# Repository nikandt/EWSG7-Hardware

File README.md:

# PP7 Hardware

This is the hardware repository of sensor probe test module, developed by student team with Aalto University.
<br>The designed system automates several tedious tasks within sensor application development by allowing easy flashing of devices without making physical changes to the test environment.

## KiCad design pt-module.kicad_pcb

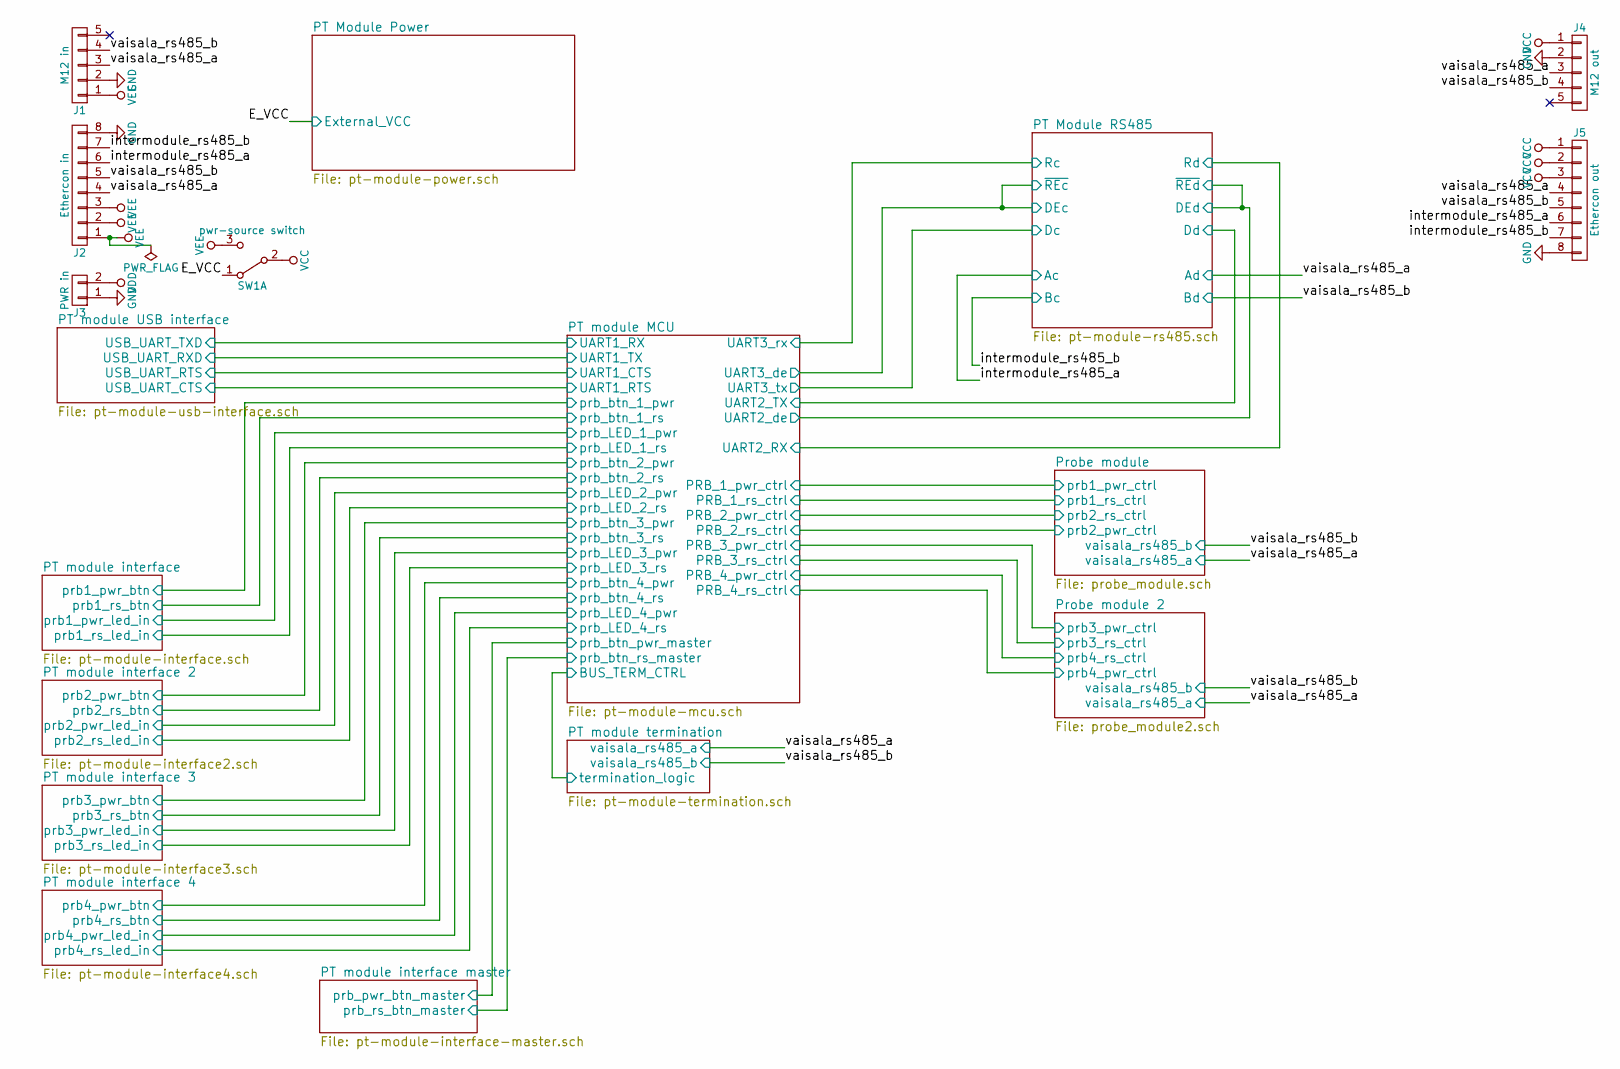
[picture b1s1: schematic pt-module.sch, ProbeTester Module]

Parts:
J1: M12 in; Hirose_DF13C-05P-1.25V_05x1.25mm_Straight
J2: Ethercon in; Hirose_DF13C-08P-1.25V_08x1.25mm_Straight
J3: PWR in; Hirose_DF13C-02P-1.25V_02x1.25mm_Straight
J4: M12 out; Hirose_DF13C-05P-1.25V_05x1.25mm_Straight
J5: Ethercon out; Hirose_DF13C-08P-1.25V_08x1.25mm_Straight
SW1: pwr-source switch; Hirose_DF13C-03P-1.25V_03x1.25mm_Straight

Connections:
/E_VCC: SW1.1 (A); also elsewhere on the board
/intermodule_rs485_a: J2.6, J5.6; also elsewhere on the board
/intermodule_rs485_b: J2.7, J5.7; also elsewhere on the board
/vaisala_rs485_a: J1.3, J2.4, J4.3, J5.4; also elsewhere on the board
/vaisala_rs485_b: J1.4, J2.5, J4.4, J5.5; also elsewhere on the board
GND: J1.2, J2.8, J3.1, J4.2, J5.8; also elsewhere on the board
VCC: J4.1, J5.1, J5.2, J5.3, SW1.2 (B); also elsewhere on the board
VDD: J3.2; also elsewhere on the board
VEE: J1.1, J2.1, J2.2, J2.3, SW1.3 (C)

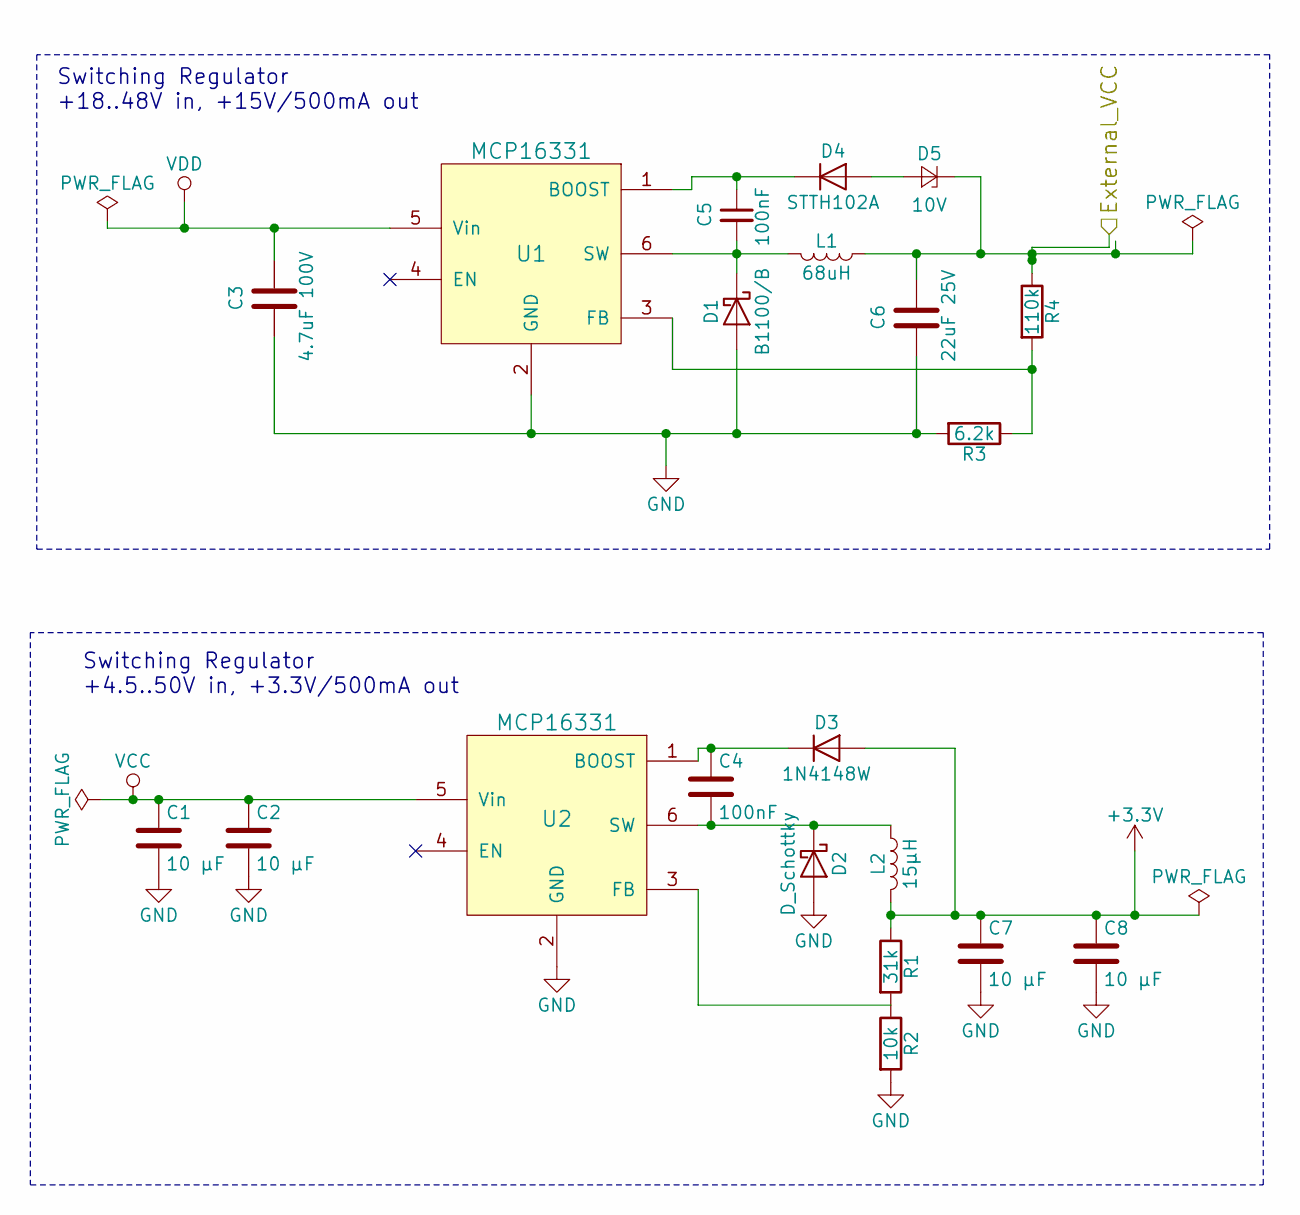
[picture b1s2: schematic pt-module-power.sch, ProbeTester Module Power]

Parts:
C1, C2, C7, C8: 10 µF; C_1206_HandSoldering
C3: 4.7uF 100V; C_1206_HandSoldering
C4, C5: 100nF; C_1206_HandSoldering
C6: 22uF 25V; C_1206_HandSoldering
D1: B1100/B; D_SMB
D2: D_Schottky; D_SMA
D3: 1N4148W; D_SOD-123F
D4: STTH102A; D_SMA
D5: 10V; D_SOD-323
L1: 68uH; L_7.3x7.3_H4.5
L2: 15µH; SM-4.3x4.3
R1: 31k; R_1206_HandSoldering
R2: 10k; R_1206_HandSoldering
R3: 6.2k; R_1206_HandSoldering
R4: 110k; R_1206_HandSoldering
U1, U2: MCP16331; SOT-23-6

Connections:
/E_VCC: C6.1, D5.1 (K), L1.1, R4.1; also elsewhere on the board
GND: C1.2, C2.2, C3.2, C6.2, C7.2, C8.2, D1.2 (A), D2.2 (A), R2.2, R3.2, U1.2 (GND), U2.2 (GND); also elsewhere on the board
unnamed: C4.1, D3.1 (K), U2.1 (BOOST)
unnamed: C4.2, D2.1 (K), L2.1, U2.6 (SW)
unnamed: C5.1, D4.1 (K), U1.1 (BOOST)
unnamed: C5.2, D1.1 (K), L1.2, U1.6 (SW)
unnamed: D4.2 (A), D5.2 (A)
unnamed: R1.2, R2.1, U2.3 (FB)
unnamed: R3.1, R4.2, U1.3 (FB)
VCC: C1.1, C2.1, U2.5 (Vin); also elsewhere on the board
VDD: C3.1, U1.5 (Vin); also elsewhere on the board

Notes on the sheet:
Switching Regulator +4.5..50V in, +3.3V/500mA out
Switching Regulator +18..48V in, +15V/500mA out

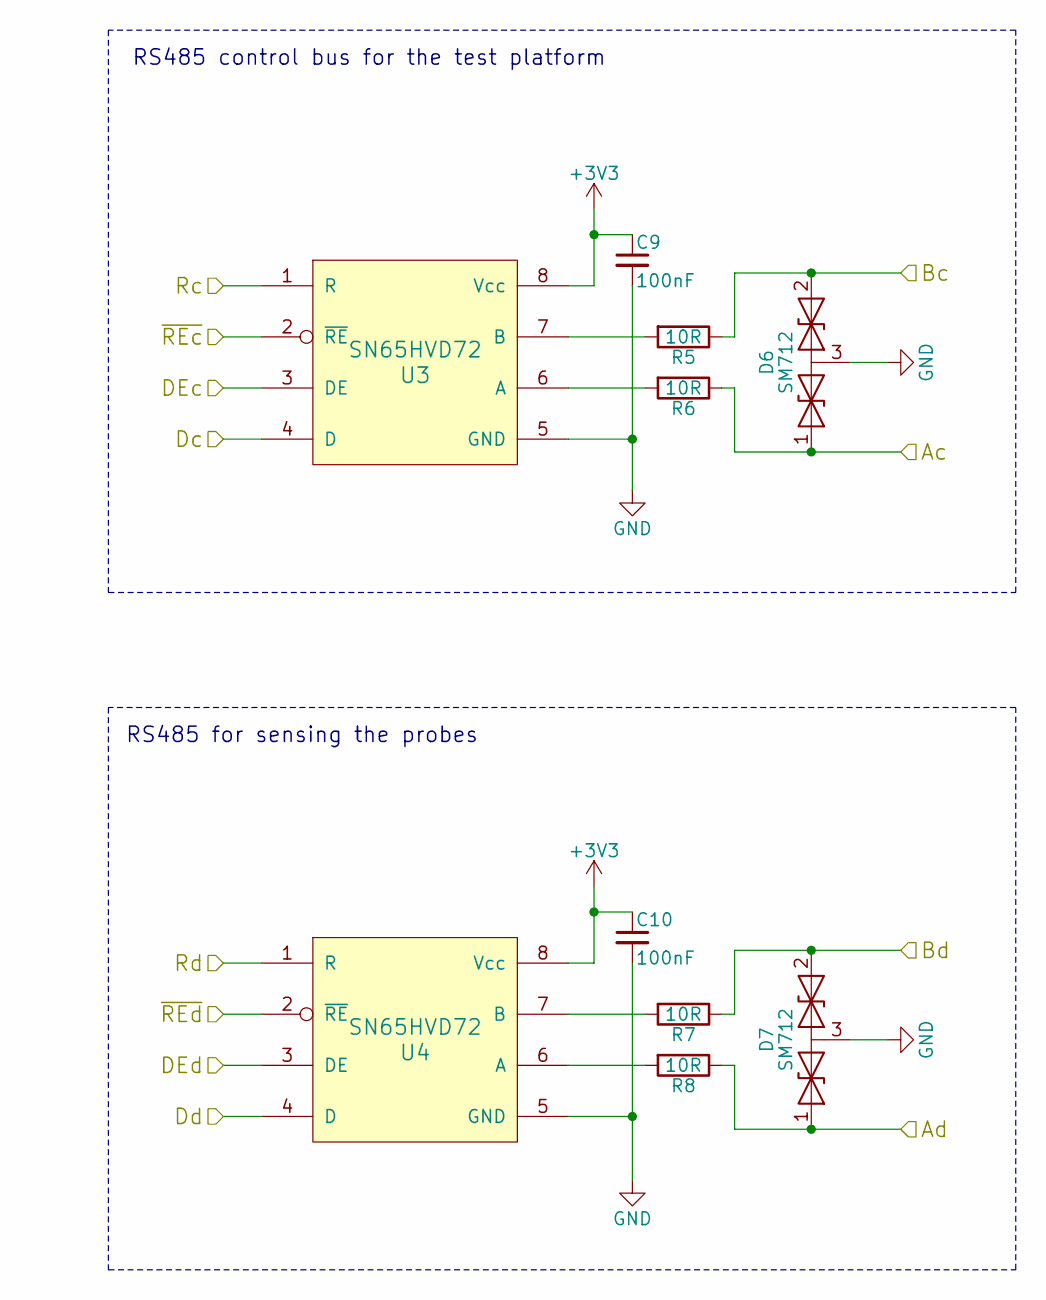
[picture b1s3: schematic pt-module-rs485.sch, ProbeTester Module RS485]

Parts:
C9, C10: 100nF; C_1206_HandSoldering
D6, D7: SM712; SOT-23_Handsoldering
R5, R6, R7, R8: 10R; R_0805_HandSoldering
U3, U4: SN65HVD72; SOIC-8_3.9x4.9mm_Pitch1.27mm

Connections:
/PT Module RS485/DEc: U3.2 (~RE), U3.3 (DE); also elsewhere on the board
/PT Module RS485/DEd: U4.2 (~RE), U4.3 (DE); also elsewhere on the board
/PT Module RS485/Dc: U3.4 (D); also elsewhere on the board
/PT Module RS485/Dd: U4.4 (D); also elsewhere on the board
/PT Module RS485/Rc: U3.1 (R); also elsewhere on the board
/PT Module RS485/Rd: U4.1 (R); also elsewhere on the board
/intermodule_rs485_a: D6.1 (A1), R6.1; also elsewhere on the board
/intermodule_rs485_b: D6.2 (A2), R5.1; also elsewhere on the board
/vaisala_rs485_a: D7.1 (A1), R8.1; also elsewhere on the board
/vaisala_rs485_b: D7.2 (A2), R7.1; also elsewhere on the board
GND: C9.2, C10.2, D6.3 (common), D7.3 (common), U3.5 (GND), U4.5 (GND); also elsewhere on the board
unnamed: R5.2, U3.7 (B)
unnamed: R6.2, U3.6 (A)
unnamed: R7.2, U4.7 (B)
unnamed: R8.2, U4.6 (A)

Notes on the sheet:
RS485 for sensing the probes
RS485 control bus for the test platform

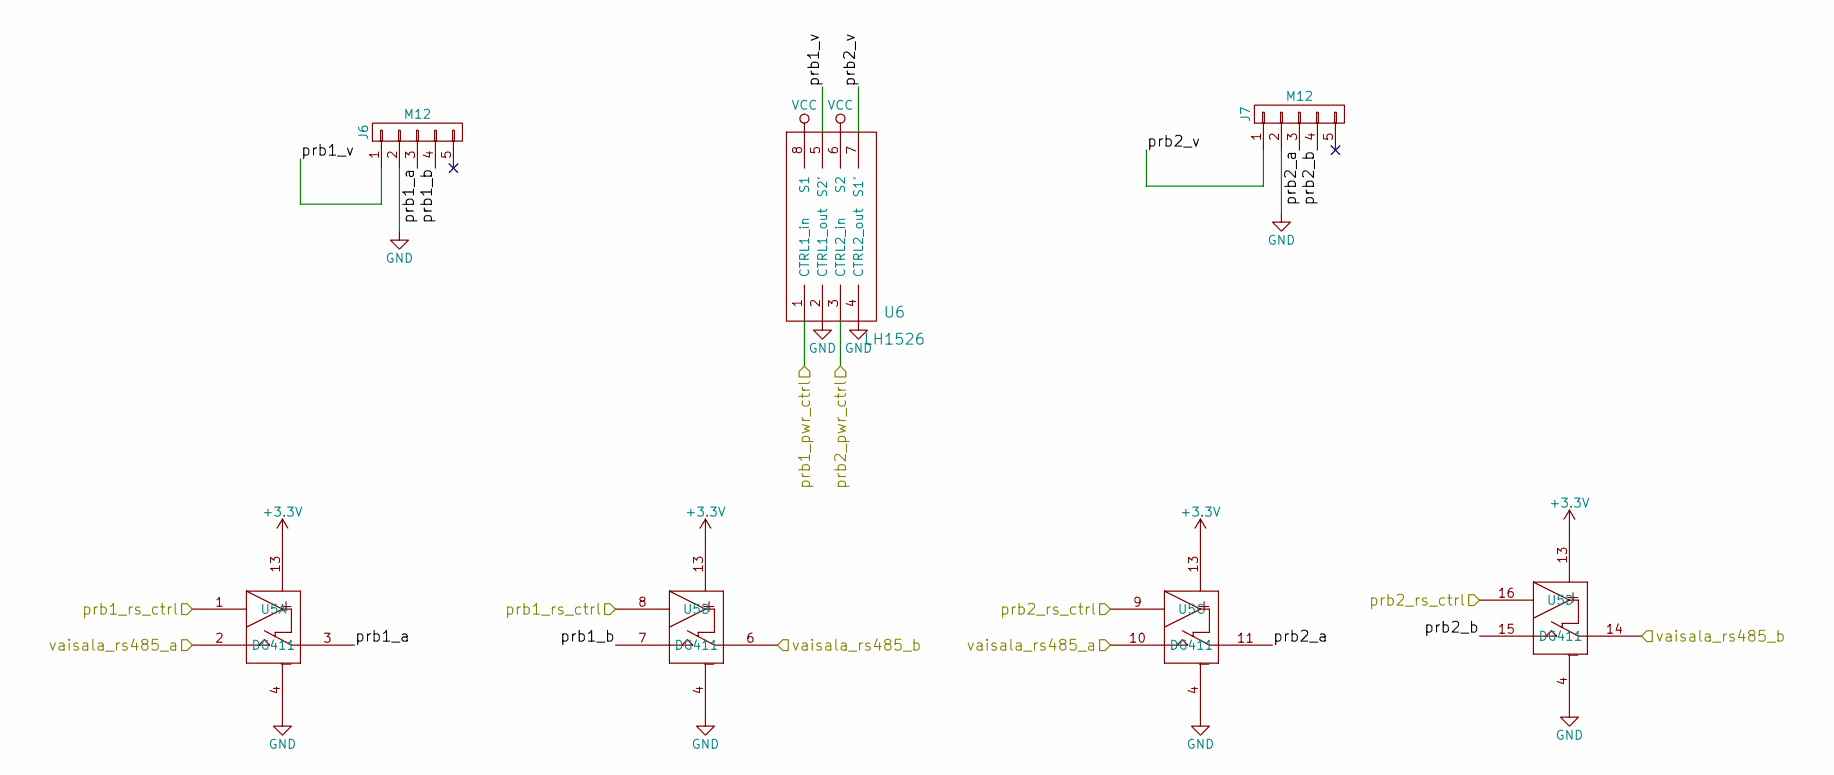
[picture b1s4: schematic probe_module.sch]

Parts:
J6, J7: M12; Hirose_DF13C-05P-1.25V_05x1.25mm_Straight
U5: DG411; DIP-16_W7.62mm_SMD
U6: LH1526; DIP-8_W9.53mm_SMD

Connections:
/PT module MCU/PRB_1_pwr_ctrl: U6.1 (CTRL1_in); also elsewhere on the board
/PT module MCU/PRB_1_rs_ctrl: U5.1 (SW), U5.8 (SW); also elsewhere on the board
/PT module MCU/PRB_2_pwr_ctrl: U5.9 (SW), U5.16 (SW); also elsewhere on the board
/PT module MCU/PRB_2_rs_ctrl: U6.3 (CTRL2_in); also elsewhere on the board
/Probe module/prb1_a: J6.3, U5.3 (OUT)
/Probe module/prb1_b: J6.4, U5.7 (IN)
/Probe module/prb1_v: J6.1, U6.5 (S2')
/Probe module/prb2_a: J7.3, U5.11 (OUT)
/Probe module/prb2_b: J7.4, U5.15 (IN)
/Probe module/prb2_v: J7.1, U6.7 (S1')
/vaisala_rs485_a: U5.2 (IN), U5.10 (IN); also elsewhere on the board
/vaisala_rs485_b: U5.6 (OUT), U5.14 (OUT); also elsewhere on the board
GND: J6.2, J7.2, U5.4 (V-), U5.5 (GND), U6.2 (CTRL1_out), U6.4 (CTRL2_out); also elsewhere on the board
VCC: U5.12 (VCC), U6.6 (S2), U6.8 (S1); also elsewhere on the board

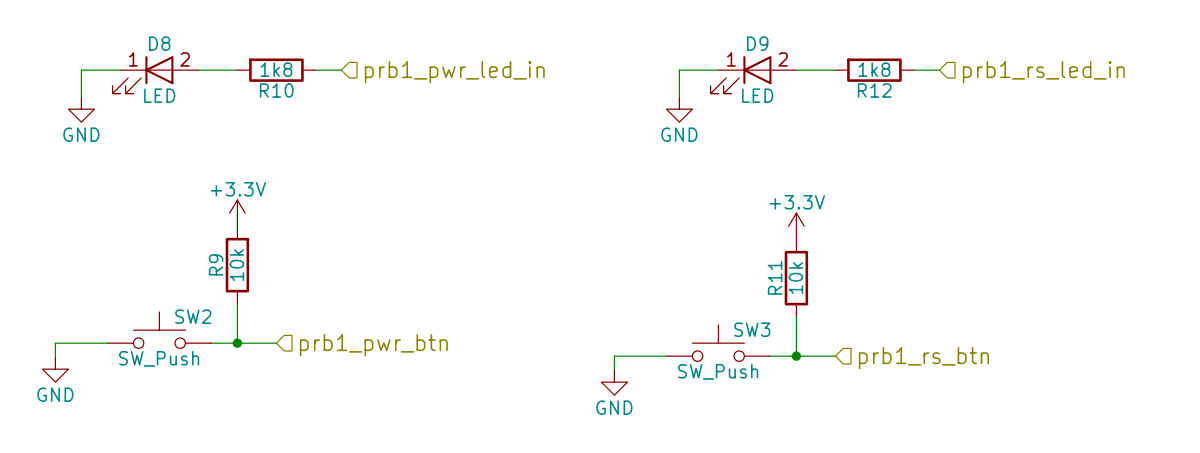
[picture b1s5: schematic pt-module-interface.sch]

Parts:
D8, D9: LED; Hirose_DF13C-02P-1.25V_02x1.25mm_Straight
R9, R11: 10k; R_1206_HandSoldering
R10, R12: 1k8; R_1206_HandSoldering
SW2, SW3: SW_Push; Hirose_DF13C-02P-1.25V_02x1.25mm_Straight

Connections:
/PT module interface/prb1_pwr_btn: R9.1, SW2.2; also elsewhere on the board
/PT module interface/prb1_pwr_led_in: R10.1; also elsewhere on the board
/PT module interface/prb1_rs_btn: R11.1, SW3.2; also elsewhere on the board
/PT module interface/prb1_rs_led_in: R12.1; also elsewhere on the board
GND: D8.1 (K), D9.1 (K), SW2.1, SW3.1; also elsewhere on the board
unnamed: D8.2 (A), R10.2
unnamed: D9.2 (A), R12.2

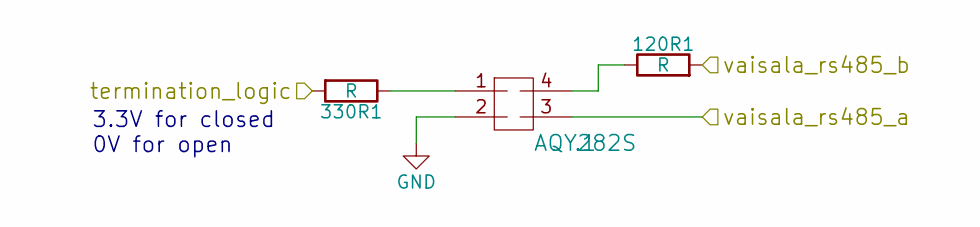
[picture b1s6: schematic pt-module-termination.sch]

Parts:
120R1: R; R_Axial_DIN0207_L6.3mm_D2.5mm_P7.62mm_Horizontal
330R1: R; R_1206_HandSoldering
.1: AQY282S; DIP-8_W11.48mm_SMD

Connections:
unnamed 57: 330R1.1, .1.1; also elsewhere on the board
unnamed 58: 120R1.1, .1.4; also elsewhere on the board

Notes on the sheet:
3.3V for closed 0V for open

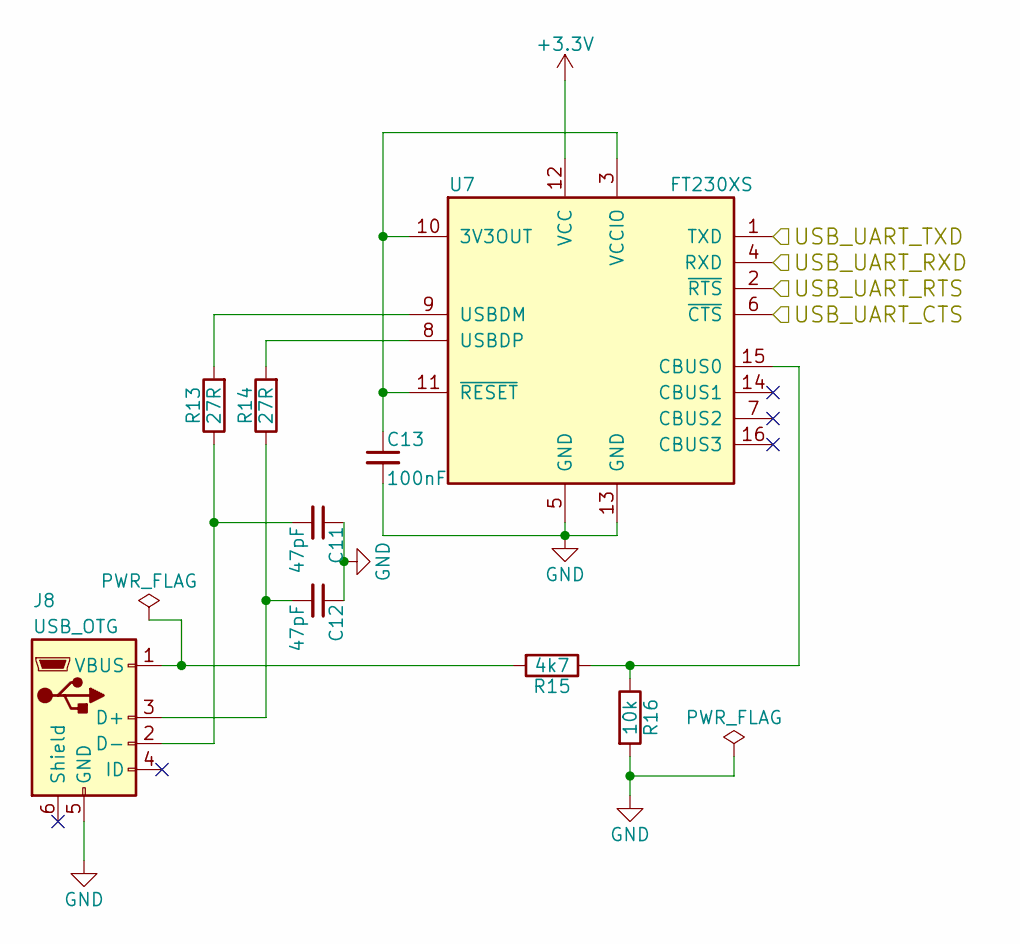
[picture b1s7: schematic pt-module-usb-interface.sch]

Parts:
C11, C12: 47pF; C_1206_HandSoldering
C13: 100nF; C_1206_HandSoldering
J8: USB_OTG; Hirose_DF13C-06P-1.25V_06x1.25mm_Straight
R13, R14: 27R; R_1206_HandSoldering
R15: 4k7; R_1206_HandSoldering
R16: 10k; R_1206_HandSoldering
U7: FT230XS; SSOP-16_3.9x4.9mm_Pitch0.635mm

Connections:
/PT module MCU/UART1_CTS: U7.2 (~RTS); also elsewhere on the board
/PT module MCU/UART1_RTS: U7.6 (~CTS); also elsewhere on the board
/PT module MCU/UART1_RX: U7.1 (TXD); also elsewhere on the board
/PT module MCU/UART1_TX: U7.4 (RXD); also elsewhere on the board
GND: C11.1, C12.1, C13.2, J8.5 (GND), R16.2, U7.5 (GND), U7.13 (GND); also elsewhere on the board
unnamed: C11.2, J8.2 (D-), R13.1
unnamed: C12.2, J8.3 (D+), R14.1
unnamed: C13.1, U7.3 (VCCIO), U7.10 (3V3OUT), U7.11 (~RESET)
unnamed: J8.1 (VBUS), R15.2
unnamed: R13.2, U7.9 (USBDM)
unnamed: R14.2, U7.8 (USBDP)
unnamed: R15.1, R16.1, U7.15 (CBUS0)

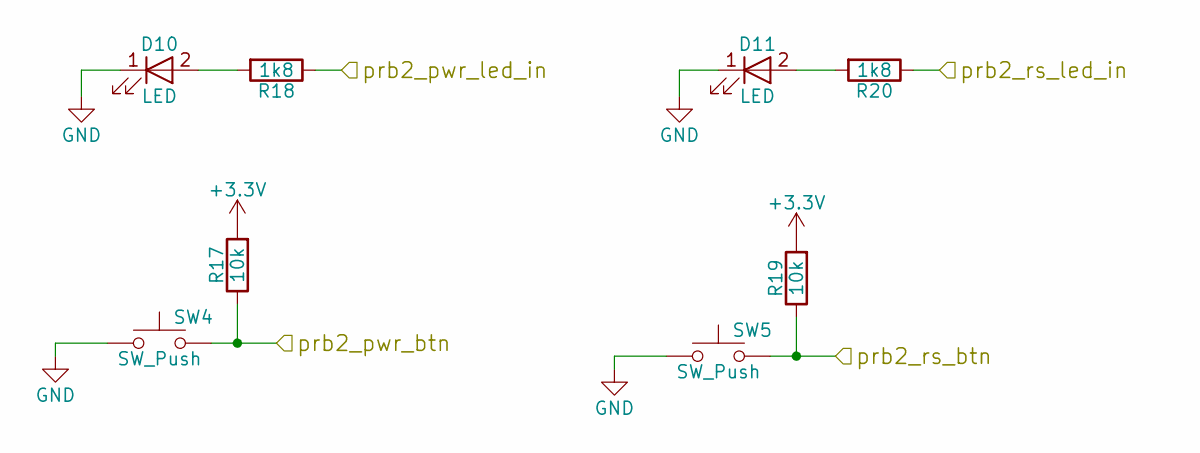
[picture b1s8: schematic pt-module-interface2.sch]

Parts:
D10, D11: LED; Hirose_DF13C-02P-1.25V_02x1.25mm_Straight
R17, R19: 10k; R_1206_HandSoldering
R18, R20: 1k8; R_1206_HandSoldering
SW4, SW5: SW_Push; Hirose_DF13C-02P-1.25V_02x1.25mm_Straight

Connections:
/PT module interface 2/prb2_pwr_btn: R17.1, SW4.2; also elsewhere on the board
/PT module interface 2/prb2_pwr_led_in: R18.1; also elsewhere on the board
/PT module interface 2/prb2_rs_btn: R19.1, SW5.2; also elsewhere on the board
/PT module interface 2/prb2_rs_led_in: R20.1; also elsewhere on the board
GND: D10.1 (K), D11.1 (K), SW4.1, SW5.1; also elsewhere on the board
unnamed: D10.2 (A), R18.2
unnamed: D11.2 (A), R20.2

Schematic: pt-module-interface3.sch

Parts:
D12, D13: LED; Hirose_DF13C-02P-1.25V_02x1.25mm_Straight
R21, R23: 10k; R_1206_HandSoldering
R22, R24: 1k8; R_1206_HandSoldering
SW6, SW7: SW_Push; Hirose_DF13C-02P-1.25V_02x1.25mm_Straight

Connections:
/PT module interface 3/prb3_pwr_btn: R21.1, SW6.2; also elsewhere on the board
/PT module interface 3/prb3_pwr_led_in: R22.1; also elsewhere on the board
/PT module interface 3/prb3_rs_btn: R23.1, SW7.2; also elsewhere on the board
/PT module interface 3/prb3_rs_led_in: R24.1; also elsewhere on the board
GND: D12.1 (K), D13.1 (K), SW6.1, SW7.1; also elsewhere on the board
unnamed: D12.2 (A), R22.2
unnamed: D13.2 (A), R24.2

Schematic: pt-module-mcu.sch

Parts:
16Mhz1: Crystal; HC49_Crystal
C14, C15: 27pF; C_1206_HandSoldering
C16, C17, C18, C19, C20, C21: C_Small; C_1206_HandSoldering
R25, R26: 10k; R_1206_HandSoldering
SW8, SW9: SW_Push; Hirose_DF13C-02P-1.25V_02x1.25mm_Straight
U8: STM32F334R8Tx; LQFP-64_10x10mm_Pitch0.5mm

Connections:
/PT Module RS485/DEc: U8.35 (ADC2_IN14/HRTIM1_CHD1/OPAMP2_VINP/OPAMP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); also elsewhere on the board
/PT Module RS485/DEd: U8.15 (ADC1_IN2/RTC_REFIN/TIM15_CH1N/TIM2_CH2/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); also elsewhere on the board
/PT Module RS485/Dc: U8.62 (CAN_TX/COMP2_OUT/DAC1_EXTI9/DAC2_EXTI9/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); also elsewhere on the board
/PT Module RS485/Dd: U8.16 (ADC1_IN3/COMP2_INM/COMP2_OUT/TIM15_CH1/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); also elsewhere on the board
/PT Module RS485/Rc: U8.61 (CAN_RX/HRTIM1_EEV8/I2C1_SCL/TIM16_CH1/T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); also elsewhere on the board
/PT Module RS485/Rd: U8.17 (ADC1_IN4/TIM15_CH2/TIM2_CH4/TSC_G1_IO4/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); also elsewhere on the board
/PT module MCU/BUS_TERM_CTRL: U8.36 (ADC2_IN15/COMP6_INM/HRTIM1_CHD2/RTC_REF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); also elsewhere on the board
/PT module MCU/PRB_1_pwr_ctrl: U8.22 (ADC2_IN3/DAC2_OUT1/OPAMP2_DIG/OPAMP2_VO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); also elsewhere on the board
/PT module MCU/PRB_1_rs_ctrl: U8.23 (ADC2_IN4/COMP2_INP/OPAMP2_VINP/OPAMP2_V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); also elsewhere on the board
/PT module MCU/PRB_2_pwr_ctrl: U8.41 (HRTIM1_CHA1/RCC_MCO/TIM1_CH1/USART1_CK/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); also elsewhere on the board
/PT module MCU/PRB_2_rs_ctrl: U8.42 (DAC1_EXTI9/DAC2_EXTI9/HRTIM1_CHA2/TIM15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); also elsewhere on the board
/PT module MCU/PRB_3_pwr_ctrl: U8.26 (ADC1_IN11/COMP4_INP/OPAMP2_VINP/OPAMP2_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); also elsewhere on the board
/PT module MCU/PRB_3_rs_ctrl: U8.27 (ADC1_IN12/COMP4_OUT/HRTIM1_SCOUT/TIM1_C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); also elsewhere on the board
/PT module MCU/PRB_4_pwr_ctrl: U8.28 (ADC2_IN12/COMP4_INM/HRTIM1_SCIN/TSC_G3_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); also elsewhere on the board
/PT module MCU/PRB_4_rs_ctrl: U8.55 (HRTIM1_EEV9/HRTIM1_SCOUT/SPI1_SCK/SYS_J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); also elsewhere on the board
/PT module MCU/RCC_OSC_IN: 16Mhz1.1, C14.1, U8.5 (PF0/RCC_OSC_IN/TIM1_CH3N)
/PT module MCU/RCC_OSC_OUT: 16Mhz1.2, C15.1, U8.6 (PF1/RCC_OSC_OUT)
/PT module MCU/UART1_CTS: U8.44 (CAN_RX/HRTIM1_CHB2/TIM1_BKIN2/TIM1_CH1N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); also elsewhere on the board
/PT module MCU/UART1_RTS: U8.45 (CAN_TX/COMP2_OUT/HRTIM1_FLT1/TIM16_CH1/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); also elsewhere on the board
/PT module MCU/UART1_RX: U8.59 (HRTIM1_EEV3/I2C1_SDA/TIM17_CH1N/TIM3_CH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); also elsewhere on the board
/PT module MCU/UART1_TX: U8.58 (HRTIM1_EEV4/HRTIM1_SCIN/I2C1_SCL/TIM16_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); also elsewhere on the board
/PT module MCU/prb_btn_pwr_master: U8.20 (ADC2_IN1/COMP2_INM/COMP4_INM/COMP6_INM/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); also elsewhere on the board
/PT module MCU/prb_btn_rs_master: U8.21 (ADC2_IN2/DAC1_OUT2/OPAMP2_VINM/OPAMP2_V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); also elsewhere on the board
/PT module interface 2/prb2_pwr_btn: U8.24 (PC4/ADC2_IN5/TIM1_ETR/USART1_TX); also elsewhere on the board
/PT module interface 2/prb2_pwr_led_in: U8.37 (PC6/COMP6_OUT/HRTIM1_EEV10/TIM3_CH1); also elsewhere on the board
/PT module interface 2/prb2_rs_btn: U8.25 (PC5/ADC2_IN11/OPAMP2_VINM/OPAMP2_VINM_S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); also elsewhere on the board
/PT module interface 2/prb2_rs_led_in: U8.38 (PC7/HRTIM1_FLT5/TIM3_CH2); also elsewhere on the board
/PT module interface 3/prb3_pwr_btn: U8.39 (PC8/HRTIM1_CHE1/TIM3_CH3); also elsewhere on the board
/PT module interface 3/prb3_pwr_led_in: U8.51 (PC10/USART3_TX); also elsewhere on the board
/PT module interface 3/prb3_rs_btn: U8.40 (PC9/DAC1_EXTI9/DAC2_EXTI9/HRTIM1_CHE2/T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); also elsewhere on the board
/PT module interface 3/prb3_rs_led_in: U8.52 (PC11/HRTIM1_EEV2/USART3_RX); also elsewhere on the board
/PT module interface 4/prb4_pwr_btn: U8.53 (PC12/HRTIM1_EEV1/USART3_CK); also elsewhere on the board
/PT module interface 4/prb4_pwr_led_in: U8.3 (PC14/RCC_OSC32_IN); also elsewhere on the board
/PT module interface 4/prb4_rs_btn: U8.2 (PC13/RTC_OUT_ALARM/RTC_OUT_CALIB/RTC_TA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); also elsewhere on the board
/PT module interface 4/prb4_rs_led_in: U8.4 (PC15/RCC_OSC32_OUT); also elsewhere on the board
/PT module interface/prb1_pwr_btn: U8.8 (PC0/ADC1_IN6/ADC2_IN6/TIM1_CH1); also elsewhere on the board
/PT module interface/prb1_pwr_led_in: U8.10 (PC2/ADC1_IN8/ADC2_IN8/TIM1_CH3); also elsewhere on the board
/PT module interface/prb1_rs_btn: U8.9 (PC1/ADC1_IN7/ADC2_IN7/TIM1_CH2); also elsewhere on the board
/PT module interface/prb1_rs_led_in: U8.11 (PC3/ADC1_IN9/ADC2_IN9/TIM1_BKIN2/TIM1_C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); also elsewhere on the board
GND: C14.2, C15.2, C16.1, C17.1, C18.1, C19.1, C20.1, C21.1, R25.1, SW9.1, U8.12 (VSSA), U8.18 (VSS), U8.31 (VSS), U8.47 (VSS), U8.63 (VSS); also elsewhere on the board
unnamed: R25.2, SW8.2, U8.60 (BOOT0)
unnamed: R26.2, SW9.2, U8.7 (NRST)

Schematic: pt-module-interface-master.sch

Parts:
R27, R28: 10k; R_1206_HandSoldering
SW10, SW11: SW_Push; Hirose_DF13C-02P-1.25V_02x1.25mm_Straight

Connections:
/PT module MCU/prb_btn_pwr_master: R27.2, SW10.2; also elsewhere on the board
/PT module MCU/prb_btn_rs_master: R28.2, SW11.2; also elsewhere on the board
GND: SW10.1, SW11.1; also elsewhere on the board

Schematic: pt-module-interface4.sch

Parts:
D14, D15: LED; Hirose_DF13C-02P-1.25V_02x1.25mm_Straight
R29, R31: 10k; R_1206_HandSoldering
R30, R32: 1k8; R_1206_HandSoldering
SW12, SW13: SW_Push; Hirose_DF13C-02P-1.25V_02x1.25mm_Straight

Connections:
/PT module interface 4/prb4_pwr_btn: R29.1, SW12.2; also elsewhere on the board
/PT module interface 4/prb4_pwr_led_in: R30.1; also elsewhere on the board
/PT module interface 4/prb4_rs_btn: R31.1, SW13.2; also elsewhere on the board
/PT module interface 4/prb4_rs_led_in: R32.1; also elsewhere on the board
GND: D14.1 (K), D15.1 (K), SW12.1, SW13.1; also elsewhere on the board
unnamed: D14.2 (A), R30.2
unnamed: D15.2 (A), R32.2

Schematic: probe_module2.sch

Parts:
J9, J10: M12; Hirose_DF13C-05P-1.25V_05x1.25mm_Straight
U9: DG411; DIP-16_W7.62mm_SMD
U10: LH1526; DIP-8_W9.53mm_SMD

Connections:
/PT module MCU/PRB_3_pwr_ctrl: U10.1 (CTRL1_in); also elsewhere on the board
/PT module MCU/PRB_3_rs_ctrl: U9.1 (SW), U9.8 (SW); also elsewhere on the board
/PT module MCU/PRB_4_pwr_ctrl: U9.9 (SW), U9.16 (SW); also elsewhere on the board
/PT module MCU/PRB_4_rs_ctrl: U10.3 (CTRL2_in); also elsewhere on the board
/Probe module 2/prb1_a: J9.3, U9.3 (OUT)
/Probe module 2/prb1_b: J9.4, U9.7 (IN)
/Probe module 2/prb1_v: J9.1, U10.5 (S2')
/Probe module 2/prb2_a: J10.3, U9.11 (OUT)
/Probe module 2/prb2_b: J10.4, U9.15 (IN)
/Probe module 2/prb2_v: J10.1, U10.7 (S1')
/vaisala_rs485_a: U9.2 (IN), U9.10 (IN); also elsewhere on the board
/vaisala_rs485_b: U9.6 (OUT), U9.14 (OUT); also elsewhere on the board
GND: J9.2, J10.2, U9.4 (V-), U9.5 (GND), U10.2 (CTRL1_out), U10.4 (CTRL2_out); also elsewhere on the board
VCC: U9.12 (VCC), U10.6 (S2), U10.8 (S1); also elsewhere on the board

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
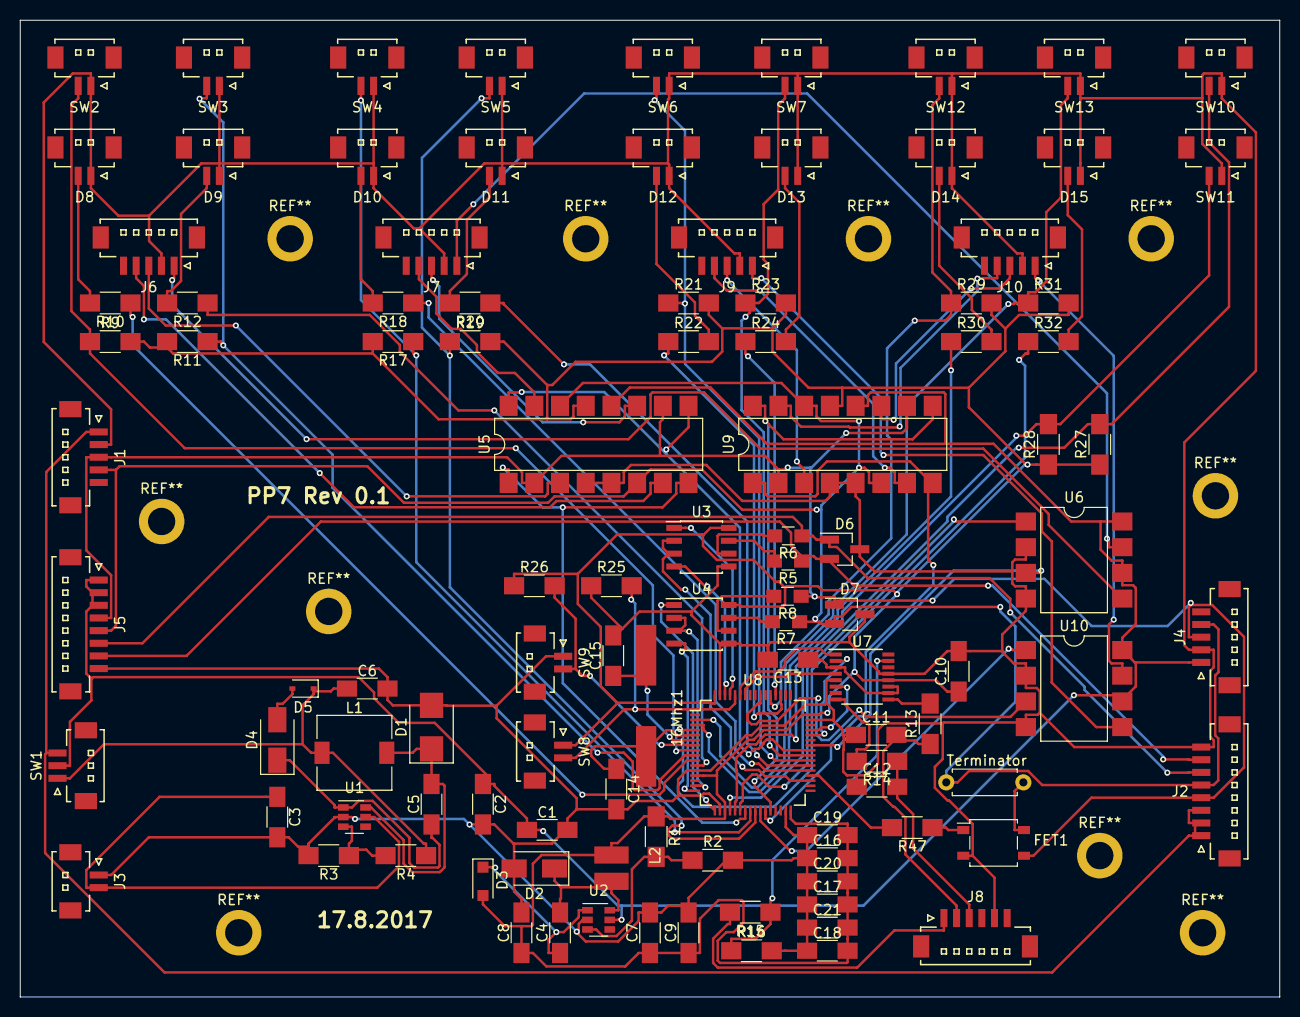
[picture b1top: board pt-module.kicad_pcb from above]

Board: 2 copper layers, 124.5 x 96.5 mm, 107 parts (0 on the bottom side), 91 nets.

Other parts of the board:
FET1: AQY282S; SO-4_4.4x4.3mm_Pitch2.54mm
R47: 330R; R_1206_HandSoldering
Terminator: R; R_Axial_DIN0207_L6.3mm_D2.5mm_P7.62mm_Horizontal

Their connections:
/PT module MCU/BUS_TERM_CTRL: R47.2; also elsewhere on the board
/vaisala_rs485_a: FET1.3; also elsewhere on the board
/vaisala_rs485_b: Terminator.2; also elsewhere on the board
GND: FET1.2; also elsewhere on the board
unnamed 57: FET1.1, R47.1; also elsewhere on the board
unnamed 58: FET1.4, Terminator.1; also elsewhere on the board

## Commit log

2017-07-28 add power schematic
2017-07-29 remove backup file
2017-07-29 add rs485 schematic
2017-08-02 MCU schematics added
2017-08-02 add probe module
2017-08-02 add interface module
2017-08-02 add vaisala bus
2017-08-02 add connectors
2017-08-02 add power connections
2017-08-03 add termination
2017-08-03 Added USB to UART interface
2017-08-03 Added USB UART hierarchical connection
2017-08-03 Added another rs485 link to MCU
2017-08-03 add resistor values
2017-08-03 Added resistor and capacitor values in MCU sheet.
2017-08-04 Fixed vusb_sense connection mistake
2017-08-08 add regulator suggestion
2017-08-08 add capacitor values
2017-08-08 I made a connect
2017-08-08 indeces to interfacemodules
2017-08-08 I don't know what I did
2017-08-08 add libraries
2017-08-08 add ssr component
2017-08-08 change probe powerswitch to ssr
2017-08-08 multiply probe modules
2017-08-09 add termination switch
2017-08-15 Fixed missing components
2017-08-15 Connected EVERYTHING. Ran ERC. There are still some power errors.
2017-08-16 fix power scheme
2017-08-16 USB interface fix
2017-08-16 Re-annotation
2017-08-16 Added power flags and ERC error count shrinked into 3.
2017-08-16 Only 1 error in ERC check. It's in PWREN.
2017-08-16 Determined MCU power capacitor sizes, at last
2017-08-16 add footprints
2017-08-17 add all the rest of the footprints
2017-08-17 fix footprint errors
2017-08-17 start the pcb
2017-08-17 pcb design
2017-08-17 Updated PCB
2017-08-17 bug fix
2017-08-17 add connections
2017-08-17 make gerbers
2017-08-22 Add LICENSE file
